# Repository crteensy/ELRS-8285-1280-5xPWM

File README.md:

# ELRS-8285-1280-5xPWM
ELRS receiver with an SX1280/1281 and 5 PWM outputs, based on the ESP8285.

see https://github.com/ExpressLRS/ExpressLRS/pull/998 for what happened earlier.

- First revision for easy manual assembly: no passives smaller than 0402, single sided.
- LEDs for power (5V, 3V3) and one for ELRS
- uFl footprint, but the Molex turret should fit as well
- simple PCB trace antenna for WiFi
- initial flashing can be done through the servo header (I think)

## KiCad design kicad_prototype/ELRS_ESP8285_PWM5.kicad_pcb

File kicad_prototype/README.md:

# ELRS-8285-1280-5xPWM / KiCad prototype

## This is the prototype design for this receiver
- single sided assembly
- passives 0402 or larger

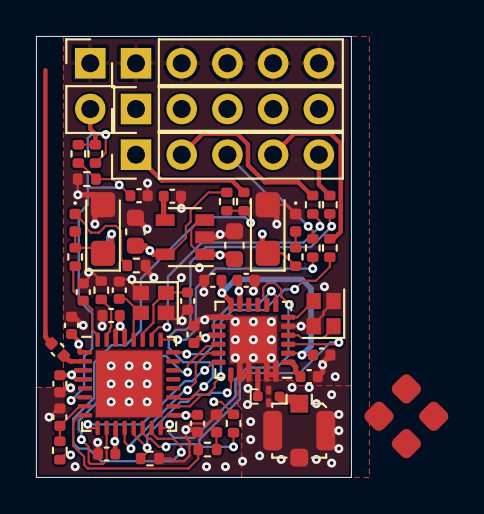
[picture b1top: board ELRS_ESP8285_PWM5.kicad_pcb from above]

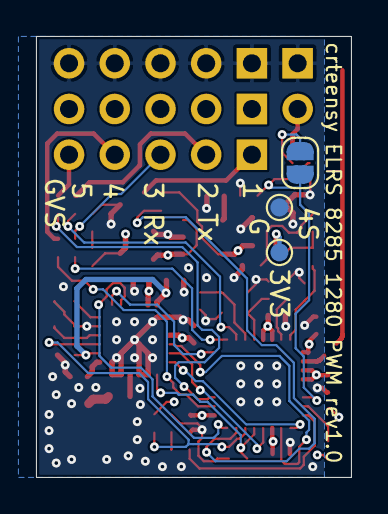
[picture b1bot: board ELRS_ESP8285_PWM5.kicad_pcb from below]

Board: 4 copper layers, 17.5 x 24.5 mm, 56 parts (3 on the bottom side), 40 nets.

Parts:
C1, C2, C3, C9, C10, C12, C15, C21: 100n; C_0402_1005Metric
C4, C11: 1u; C_0402_1005Metric
C5, C8: 100u; CP_EIA-3216-18_Kemet-A
C6: 1u; C_0603_1608Metric
C7: 4u7; C_0603_1608Metric
C13: 10p; C_0402_1005Metric
C16, C17, C22: 10n; C_0402_1005Metric
C18: 470n; C_0402_1005Metric
C19, C20: 4p7; C_0402_1005Metric
D1: blue_2V9; LED_0402_1005Metric
D2: true_gr_3V3; LED_0402_1005Metric
D4: red_2V1; LED_0402_1005Metric
J1: Conn_Coaxial; U.FL_Molex_MCRF_73412-0110_Vertical_dense
J2, J3, J4: Conn_01x05; PinHeader_1x05_P2.54mm_Vertical
J5: Conn_Coaxial; molex_479480001_2g4-turret
J6: Conn_01x02; PinHeader_1x02_P2.54mm_Vertical
JP1: 4S; SolderJumper-2_P1.3mm_Open_RoundedPad1.0x1.5mm
R1, R2, R3, R10, R13, R14: 12k; R_0402_1005Metric
R4: 560R; R_0402_1005Metric
R5, R6, R7, R8, R9, R16: 1k; R_0402_1005Metric
R11: 270R; R_0402_1005Metric
R12: 4k7; R_0402_1005Metric
R15: 24k; R_0402_1005Metric
R17: 47k; R_0402_1005Metric
TP1, TP2: TestPoint; TestPoint_Pad_D1.0mm
U1: SPX3819M5-L-3-3; SOT-23-5
U2: ESP8285; QFN-32-1EP_5x5mm_P0.5mm_EP3.7x3.7mm_dense
U5: 2450FM07D0034T
U6: SX1281; QFN-24-1EP_4x4mm_P0.5mm_EP2.6x2.6mm_SX1280_dense
Y2: 26M; Crystal_SMD_2016-4Pin_2.0x1.6mm
Y3: 52M; Crystal_SMD_2016-4Pin_2.0x1.6mm

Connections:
+3V3: C1.1, C2.1, C3.1, C7.1, C8.1, C9.1, C10.1, C15.1, C21.1, D1.2, R1.2, R3.2, R10.2, R13.2, TP1.1, U1.5, U2.1, U2.3, U2.4, U2.11, U2.17, U2.29, U2.30, U6.11, U6.15
+5V: C5.1, C6.1, J4.1, J4.2, J4.3, J4.4, J4.5, R12.1, U1.1, U1.3
ADC_sig: C12.1, JP1.2, R15.1, R16.2, U2.6
BUSY_A: U2.24, U6.7
DIO1_A: U2.16, U6.8
ESPX_IN: C20.1, U2.28, Y2.3
ESPX_OUT: C19.1, U2.27, Y2.1
ESP_EN: C4.1, R1.1, U2.7
GND: C1.2, C2.2, C3.2, C4.2, C5.2, C6.2, C7.2, C8.2, C9.2, C10.2, C11.2, C12.2, C15.2, C16.2, C17.2, C18.2, C19.2, C20.2, C21.2, C22.2, D2.1, D4.1, J1.2, J2.1, J2.2, J2.3, J2.4, J2.5, J6.1, R2.1, R11.2, R14.1, R16.1, TP2.1, U1.2, U2.33, U5.2, U5.4, U6.0, U6.5, U6.13, U6.20, U6.21, U6.23, U6.24, Y2.2, Y2.4, Y3.2, Y3.4
LED_A: R4.1, U2.8
MISO: U2.10, U6.16
MOSI: U2.12, U6.17
NRST_A: R10.1, U2.14, U6.3
NSS_A: R14.2, U2.13, U6.19
unnamed: C11.1, R3.1, U2.32
unnamed: C13.2, U2.2
unnamed: C16.1, C18.1, U6.2, U6.12
unnamed: C17.1, U6.1
unnamed: C22.1, U1.4
unnamed: D1.1, R11.1
unnamed: D2.2, R12.2
unnamed: D4.2, R4.2
unnamed: J1.1, J5.1, U5.3
unnamed: J3.1, R5.1
unnamed: J3.2, R6.1
unnamed: J3.3, R7.1
unnamed: J3.4, R8.1
unnamed: J3.5, R9.1
unnamed: J6.2, R15.2, R17.2
unnamed: JP1.1, R17.1
unnamed: R2.2, U2.31
unnamed: U5.1, U6.22
unnamed: U6.4, Y3.1
unnamed: U6.6, Y3.3
PWM1: R5.2, R13.1, U2.15
PWM2: R6.2, U2.26
PWM3: R7.2, U2.25
PWM4: R8.2, U2.18
PWM5: R9.2, U2.19
SCK: U2.9, U6.18

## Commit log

2021-10-29 remove datasheets
2021-10-29 move pogo pad to boot input, minor layout changes
2021-10-30 layout work
2021-11-01 schematic/layout rev0.3
2021-11-01 add series cap to antenna trace
2022-06-01 general update
